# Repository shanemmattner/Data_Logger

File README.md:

# Remote Data Logger
Remote data logger project for use in engineering development and debugging of electronics in the field

## Feature List

### Hardware
- ESP32-C3 circuit
- 5 ADC
- 16 GPIO
- USB-C
- uSD card
- 44mm x 33mm

### Firmware
- <span style="color:green">Written in Rust</span>
- <span style="color:green">Utilize [static](https://github.com/mdeloof/statig) heirarchical state machine</span>
- <span style="color:green">Multi-threaded</span>
- <span style="color:green">ADC reading</span>
- <span style="color:red">UART CLI</span>
- <span style="color:red">Store values to uSD card
- <span style="color:red">Connect to WiFi</span>
- <span style="color:red">Send message with MQTT</span>

### Software
- <span style="color:green">Graph readings from ESP32-C3 through UART</span>
    - [Serial Console Oscilloscope](https://github.com/shanemmattner/Serial_Console_Oscilloscope)

## Notes

### Git
Update submodules manually:
```
git submodule update  --init --recursive
```

Configure repo to use custom `.githooks` path and make files executable:
```
git config --local core.hooksPath .githooks/
chmod -R +x .githooks
```

## KiCAD Hotkeys
- `e` while routing:  change parameters of trace
- `b` re-pour copper fills
    - `ctrl + b` to remove all fills
- `u` select entire track
- `v` via when routing
    - switch to bottom when not routing
- `c` Design rule check panel
    - custom hotkey

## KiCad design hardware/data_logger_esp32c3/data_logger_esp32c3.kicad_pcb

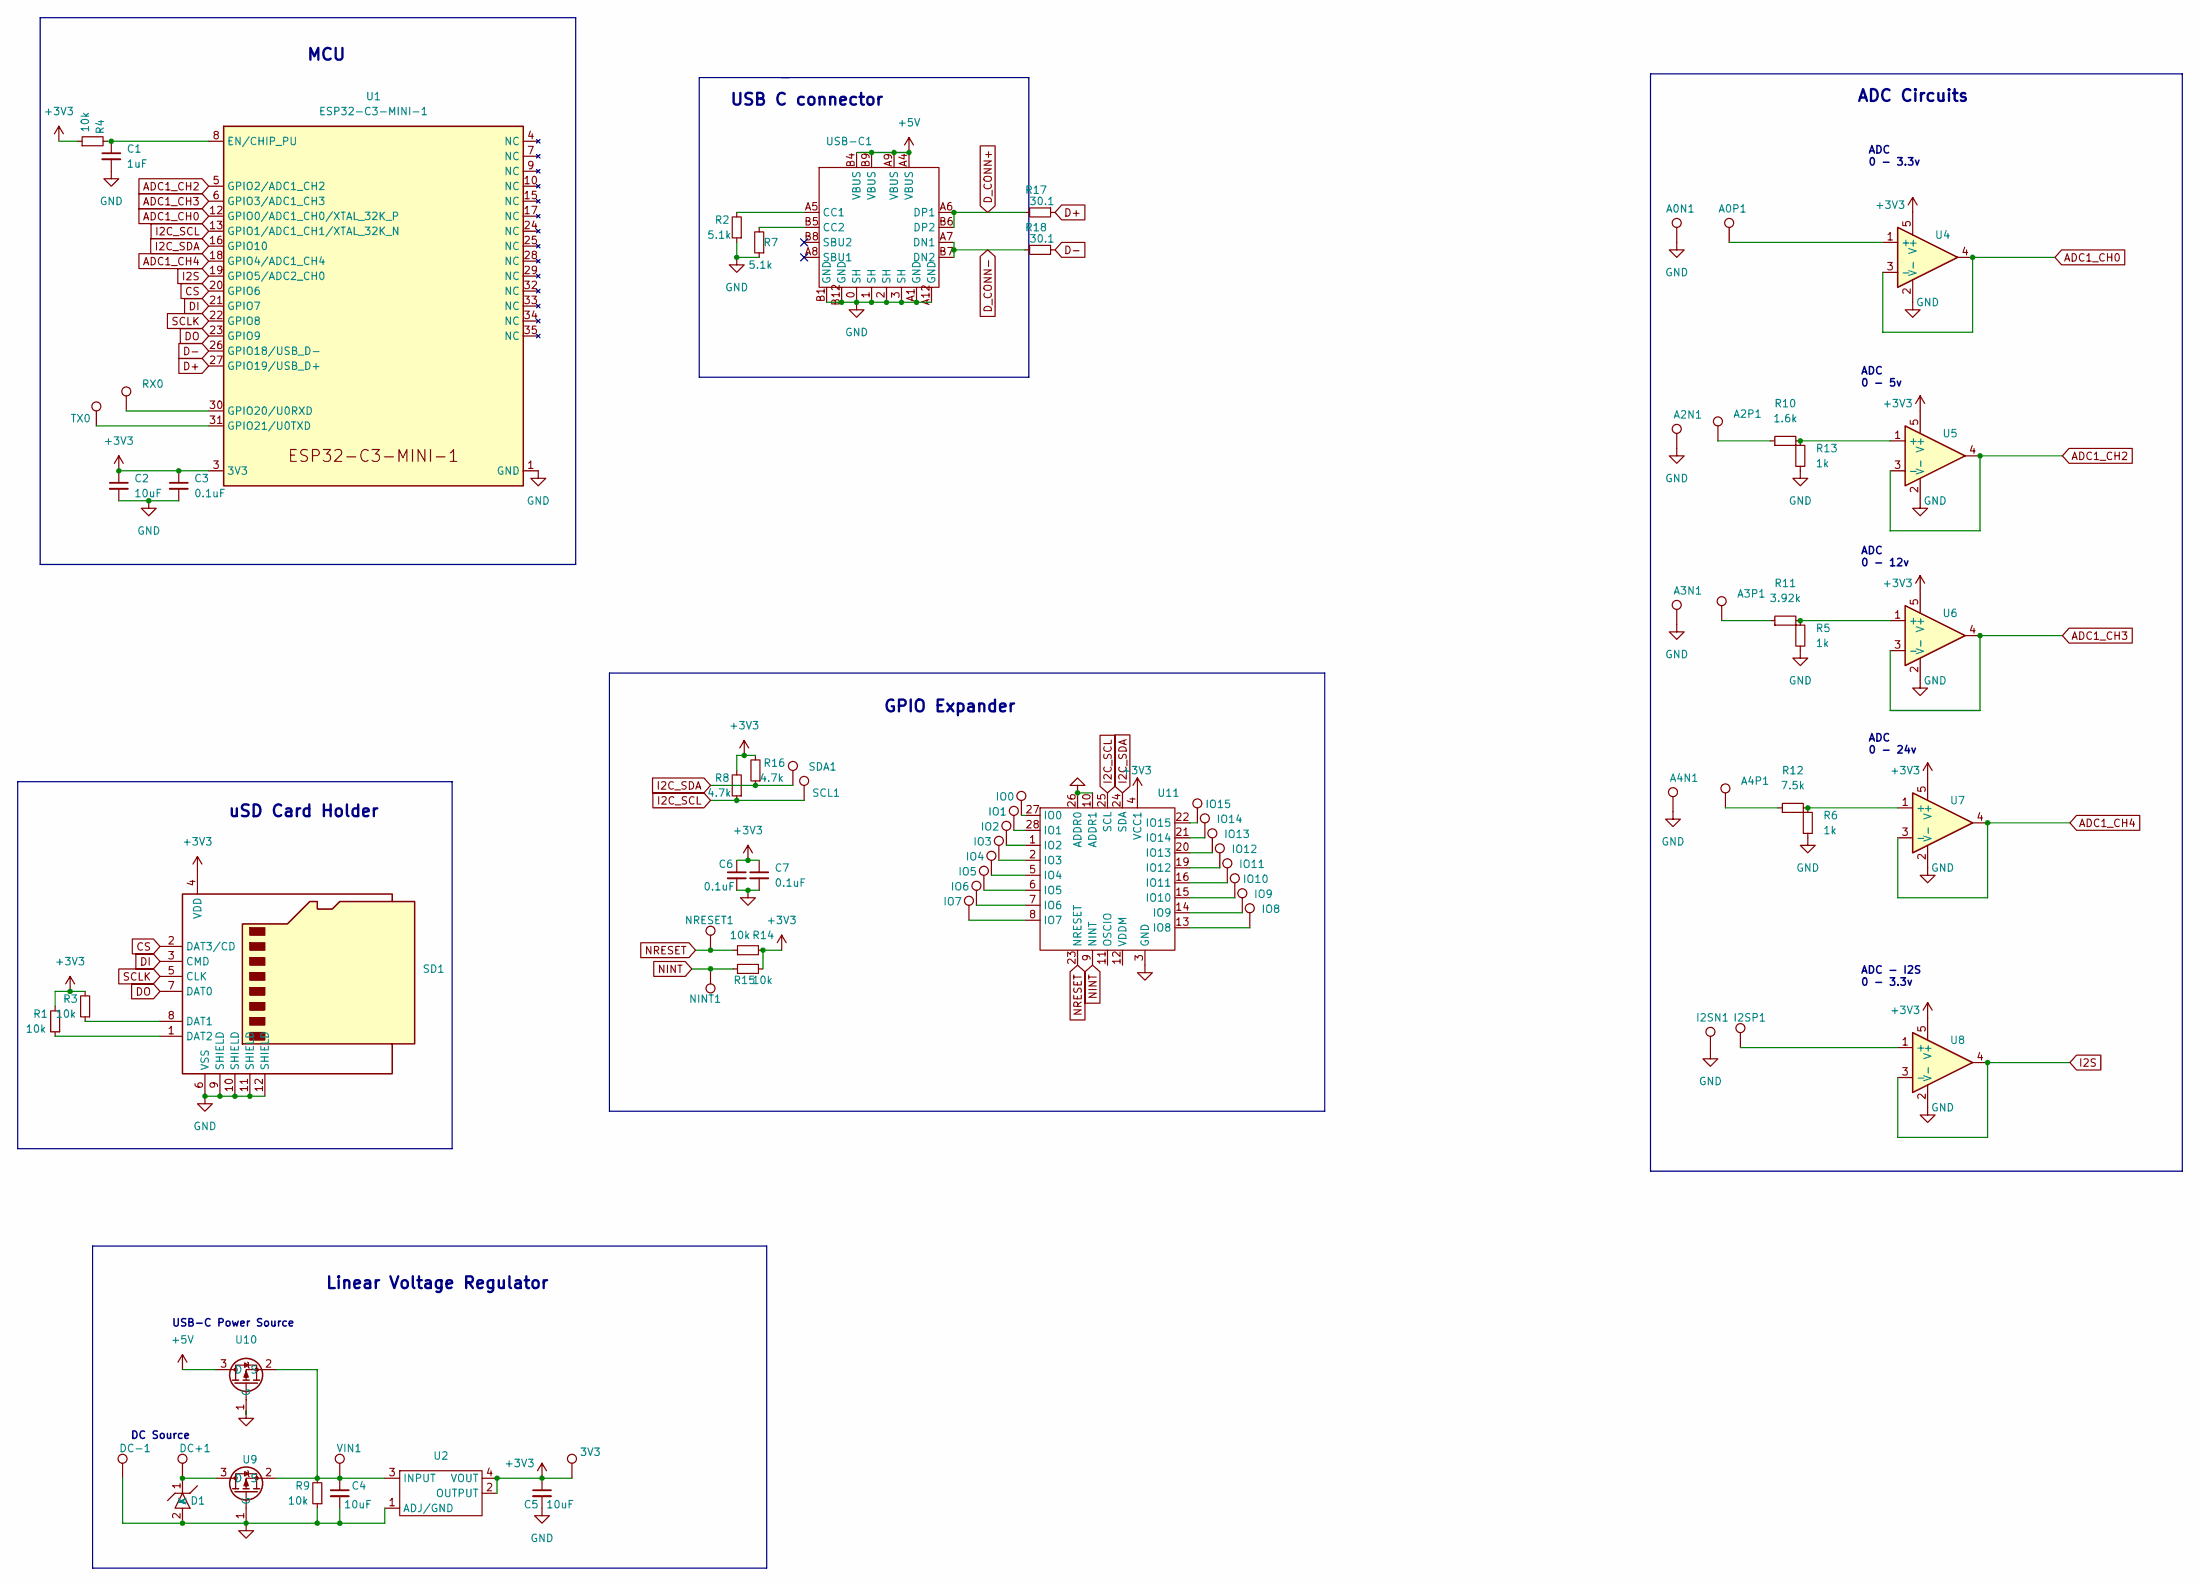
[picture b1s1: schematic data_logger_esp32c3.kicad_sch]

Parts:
3V3: TestPoint; TestPoint_THTPad_1.0x1.0mm_Drill0.5mm
A0N1, A0P1, A2N1, A2P1, A3N1, A3P1, A4N1, A4P1: TestPoint; TestPoint_THTPad_1.0x1.0mm_Drill0.5mm
C1: 1uF; C_0402_1005Metric; part_number 0402X105K6R3NT
C2, C4, C5: 10uF; C_0603_1608Metric; part_number CL10A106KO8NQNC
C3, C6, C7: 0.1uF; C_0402_1005Metric; part_number GCM155L81E104KE02D
D1: LTVS16H5.0T5G; DFN1610
DC+1: TestPoint; TestPoint_THTPad_1.0x1.0mm_Drill0.5mm
DC-1: TestPoint; TestPoint_THTPad_1.0x1.0mm_Drill0.5mm
I2SN1, I2SP1: TestPoint; TestPoint_THTPad_1.0x1.0mm_Drill0.5mm
IO0, IO1, IO2, IO3, IO4, IO5, IO6, IO7, IO8, IO9, IO10, IO11, IO12, IO13, IO14, IO15: TestPoint; TestPoint_THTPad_1.0x1.0mm_Drill0.5mm
NINT1: TestPoint; TestPoint_THTPad_1.0x1.0mm_Drill0.5mm
NRESET1: TestPoint; TestPoint_THTPad_1.0x1.0mm_Drill0.5mm
R1, R3, R4, R9, R14, R15: 10k; R_0402_1005Metric; part_number ERJ2RKF1002X
R2, R7: 5.1k; R_0402_1005Metric; part_number ERJ2RKF5101X
R5, R6, R13: 1k; R_0402_1005Metric; part_number CR-02FL6----1K
R8, R16: 4.7k; R_0402_1005Metric; part_number RC0402FR-074K7L
R10: 1.6k; R_0402_1005Metric; part_number RMC04021.6K1%N
R11: 3.92k; R_0402_1005Metric; part_number RC0402FR-073K9L
R12: 7.5k; R_0402_1005Metric; part_number AECR0402F7K50K9
R17, R18: 30.1; R_0402_1005Metric; part_number 0402WGF301JTCE
RX0: TestPoint; TestPoint_THTPad_1.0x1.0mm_Drill0.5mm
SCL1: TestPoint; TestPoint_THTPad_1.0x1.0mm_Drill0.5mm
SD1: 472192001; part_number 472192001
SDA1: TestPoint; TestPoint_THTPad_1.0x1.0mm_Drill0.5mm
TX0: TestPoint; TestPoint_THTPad_1.0x1.0mm_Drill0.5mm
U1: ESP32-C3-MINI-1
U2: AZ1117IH-3.3TRG1; SOT-223-4
U4, U5, U6, U7, U8: LM321MF; part_number LM321MF
U9, U10: A03401A; SOT-23
U11: SX1509BIULTRT; QFN-28-EP(4x4)
USB-C1: USB-TYPE-C-018
VIN1: TestPoint; TestPoint_THTPad_1.0x1.0mm_Drill0.5mm

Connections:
+3V3: 3V3.1, C2.1, C3.1, C5.1, C6.1, C7.1, R1.2, R3.2, R4.1, R8.2, R14.2, R15.2, R16.2, SD1.4 (VDD), U1.3 (3V3), U2.2 (OUTPUT), U2.4 (VOUT), U4.5 (V+), U5.5 (V+), U6.5 (V+), U7.5 (V+), U8.5 (V+), U11.4 (VCC1), U11.18 (VCC2)
+5V: U10.3 (D), USB-C1.A4 (VBUS), USB-C1.A9 (VBUS), USB-C1.B4 (VBUS), USB-C1.B9 (VBUS)
ADC1_CH0: U1.12 (GPIO0/ADC1_CH0/XTAL_32K_P), U4.3 (-), U4.4
ADC1_CH2: U1.5 (GPIO2/ADC1_CH2), U5.3 (-), U5.4
ADC1_CH3: U1.6 (GPIO3/ADC1_CH3), U6.3 (-), U6.4
ADC1_CH4: U1.18 (GPIO4/ADC1_CH4), U7.3 (-), U7.4
CS: SD1.2 (DAT3/CD), U1.20 (GPIO6)
D+: R17.1, U1.27 (GPIO19/USB_D+)
D-: R18.1, U1.26 (GPIO18/USB_D-)
DI: SD1.3 (CMD), U1.21 (GPIO7)
DO: SD1.7 (DAT0), U1.23 (GPIO9)
D_CONN+: R17.2, USB-C1.A6 (DP1), USB-C1.B6 (DP2)
D_CONN-: R18.2, USB-C1.A7 (DN1), USB-C1.B7 (DN2)
GND: A0N1.1, A2N1.1, A3N1.1, A4N1.1, C1.2, C2.2, C3.2, C4.2, C5.2, C6.2, C7.2, D1.2 (A), DC-1.1, I2SN1.1, R2.1, R5.2, R6.2, R7.1, R9.1, R13.2, SD1.6 (VSS), SD1.9 (SHIELD), SD1.10 (SHIELD), SD1.11 (SHIELD), SD1.12 (SHIELD), U1.1 (GND), U1.2 (GND), U1.11, U1.14, U1.36 (GND), U1.37 (GND), U1.38 (GND), U1.39 (GND), U1.40 (GND), U1.41 (GND), U1.42 (GND), U1.43 (GND), U1.44 (GND), U1.45 (GND), U1.46 (GND), U1.47 (GND), U1.48 (GND), U1.49 (GND), U1.50 (GND), U1.51 (GND), U1.52 (GND), U1.53 (GND), U2.1 (ADJ/GND), U4.2 (V-), U5.2 (V-), U6.2 (V-), U7.2 (V-), U8.2 (V-), U9.1 (G), U10.1 (G), U11.3 (GND), U11.10 (ADDR1), U11.17 (GND), U11.26 (ADDR0), U11.29 (PAD), USB-C1.0 (SH), USB-C1.1 (SH), USB-C1.2 (SH), USB-C1.3 (SH), USB-C1.A1 (GND), USB-C1.A12 (GND), USB-C1.B1 (GND), USB-C1.B12 (GND)
I2C_SCL: R8.1, SCL1.1, U1.13 (GPIO1/ADC1_CH1/XTAL_32K_N), U11.25 (SCL)
I2C_SDA: R16.1, SDA1.1, U1.16 (GPIO10), U11.24 (SDA)
I2S: U1.19 (GPIO5/ADC2_CH0), U8.3 (-), U8.4
NINT: NINT1.1, R15.1, U11.9 (NINT)
NRESET: NRESET1.1, R14.1, U11.23 (NRESET)
unnamed: A0P1.1, U4.1 (+)
unnamed: A2P1.1, R10.1
unnamed: A3P1.1, R11.1
unnamed: A4P1.1, R12.1
unnamed: C1.1, R4.2, U1.8 (EN/CHIP_PU)
unnamed: C4.1, R9.2, U2.3 (INPUT), U9.2 (S), U10.2 (S), VIN1.1
unnamed: D1.1 (K), DC+1.1, U9.3 (D)
unnamed: I2SP1.1, U8.1 (+)
unnamed: IO0.1, U11.27 (IO0)
unnamed: IO1.1, U11.28 (IO1)
unnamed: IO2.1, U11.1 (IO2)
unnamed: IO3.1, U11.2 (IO3)
unnamed: IO4.1, U11.5 (IO4)
unnamed: IO5.1, U11.6 (IO5)
unnamed: IO6.1, U11.7 (IO6)
unnamed: IO7.1, U11.8 (IO7)
unnamed: IO8.1, U11.13 (IO8)
unnamed: IO9.1, U11.14 (IO9)
unnamed: IO10.1, U11.15 (IO10)
unnamed: IO11.1, U11.16 (IO11)
unnamed: IO12.1, U11.19 (IO12)
unnamed: IO13.1, U11.20 (IO13)
unnamed: IO14.1, U11.21 (IO14)
unnamed: IO15.1, U11.22 (IO15)
unnamed: R1.1, SD1.1 (DAT2)
unnamed: R2.2, USB-C1.A5 (CC1)
unnamed: R3.1, SD1.8 (DAT1)
unnamed: R7.2, USB-C1.B5 (CC2)
unnamed: R10.2, R13.1, U5.1 (+)
unnamed: R5.1, R11.2, U6.1 (+)
unnamed: R6.1, R12.2, U7.1 (+)
unnamed: RX0.1, U1.30 (GPIO20/U0RXD)
unnamed: TX0.1, U1.31 (GPIO21/U0TXD)
SCLK: SD1.5 (CLK), U1.22 (GPIO8)

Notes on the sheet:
ADC Circuits
uSD Card Holder
Linear Voltage Regulator
ADC 0 - 5v
USB-C Power Source
ADC 0 - 3.3v
ADC 0 - 12v
DC Source
USB C connector
GPIO Expander
MCU
ADC 0 - 24v
ADC - I2S 0 - 3.3v

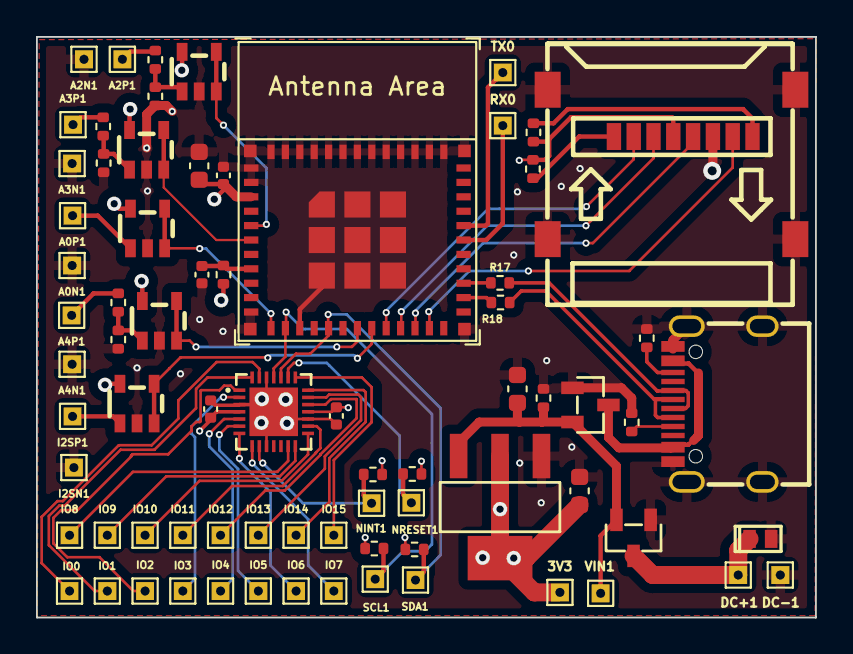
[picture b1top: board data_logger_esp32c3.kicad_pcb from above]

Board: 4 copper layers, 43.3 x 32.3 mm, 74 parts (0 on the bottom side), 53 nets.

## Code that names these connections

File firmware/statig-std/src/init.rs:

use esp_idf_hal::adc::PoweredAdc;
use esp_idf_hal::adc::{self, Atten11dB};
use esp_idf_hal::prelude::*;
use esp_idf_hal::units::FromValueType;
use esp_idf_hal::{gpio, i2c};

use sx1509;

pub struct Board {
    pub i2c1: i2c::Master<i2c::I2C0, gpio::Gpio1<gpio::InputOutput>, gpio::Gpio10<gpio::Output>>,
    pub adc1: PoweredAdc<adc::ADC1>,
    pub adc2: PoweredAdc<adc::ADC2>,
    pub adc1_ch0: gpio::Gpio0<Atten11dB<adc::ADC1>>,
    // pub adc1_ch1: gpio::Gpio1<Atten11dB<adc::ADC1>>,
    pub adc1_ch2: gpio::Gpio2<Atten11dB<adc::ADC1>>,
    pub adc1_ch3: gpio::Gpio3<Atten11dB<adc::ADC1>>,
    pub adc1_ch4: gpio::Gpio4<Atten11dB<adc::ADC1>>,
    pub adc2_ch0: gpio::Gpio5<Atten11dB<adc::ADC2>>,
    pub gpio_exp: sx1509::Sx1509<
        i2c::Master<i2c::I2C0, gpio::Gpio1<gpio::InputOutput>, gpio::Gpio10<gpio::Output>>,
    >,
    pub psh_btn: gpio::Gpio9<gpio::Input>,
    pub led: gpio::Gpio8<gpio::Output>,
}

impl Board {
    pub fn init(p: Peripherals) -> Board {
        // GPIO
        let psh_btn = p.pins.gpio9.into_input().unwrap();
        let led = p.pins.gpio8.into_output().unwrap();

        // I2C
        let sda = p.pins.gpio1.into_input_output().unwrap();
        let scl = p.pins.gpio10.into_output().unwrap();
        let i2c = p.i2c0;
        let config = <i2c::config::MasterConfig as Default>::default().baudrate(400.kHz().into());
        let mut i2c1 =
            i2c::Master::<i2c::I2C0, _, _>::new(i2c, i2c::MasterPins { sda, scl }, config).unwrap();

        // GPIO expander
        let mut expander = sx1509::Sx1509::new(&mut i2c1, sx1509::DEFAULT_ADDRESS);
        match expander.borrow(&mut i2c1).software_reset() {
            Ok(_) => log::info!("SX1509 reset"),
            Err(_) => log::info!("SX1509 error resetting"),
        }
        match expander.borrow(&mut i2c1).set_bank_a_direction(0) {
            Ok(_) => log::info!("SX1509 set bank A success"),
            Err(_) => log::info!("SX1509 error set bank A"),
        }
        match expander.borrow(&mut i2c1).set_bank_b_direction(0xFF) {
            Ok(_) => log::info!("SX1509 set bank B success"),
            Err(_) => log::info!("SX1509 error set bank B"),
        }

        // ADC
        let config = adc::config::Config::new().calibration(true);

        let adc1_ch0 = p.pins.gpio0.into_analog_atten_11db().unwrap();
        // let adc1_ch1 = p.pins.gpio1.into_analog_atten_11db().unwrap();
        let adc1_ch2 = p.pins.gpio2.into_analog_atten_11db().unwrap();
        let adc1_ch3 = p.pins.gpio3.into_analog_atten_11db().unwrap();
        let adc1_ch4 = p.pins.gpio4.into_analog_atten_11db().unwrap();
        let adc2_ch0 = p.pins.gpio5.into_analog_atten_11db().unwrap();

        let adc1 = PoweredAdc::new(p.adc1, config).unwrap();
        let adc2 = PoweredAdc::new(p.adc2, config).unwrap();

        Board {
            i2c1: i2c1,
            adc1: adc1,
            adc2: adc2,
            adc1_ch0: adc1_ch0,
            // adc1_ch1: adc1_ch1,
            adc1_ch2: adc1_ch2,
            adc1_ch3: adc1_ch3,
            adc1_ch4: adc1_ch4,
            adc2_ch0: adc2_ch0,
            gpio_exp: expander,
            psh_btn: psh_btn,
            led: led,
        }
    }
}

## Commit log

2023-01-20 Base hardware and firmware for Remote Data logger
2023-01-20 Add README
2023-01-20 Add pic of pcb
2023-01-20 documentation
2023-02-27 replaced adc with neopixel
